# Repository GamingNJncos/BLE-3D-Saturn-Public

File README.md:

# BLE-3D #
Sega Saturn 3D Controller Bluetooth(BLE) Adapter

# **What does it do?** #
- This is an open source and completely solderless adapter for the Sega Saturn 3D Controller that converts it to a Bluetooth(BLE) HID Gamepad. 
- The end result demonstrates a battery powered and solderless adapter that allows you to use one of the best controllers ever made to date across numerous consoles

### Highlights ###
- **Zero modifications to the factory controller** are neccesary to build, test, or play with this adapter.
- Both Analog, and Digital mode (switch on controller) are fully supported
- Want to revert back to OE? Simply plug the OE cable back in. 
- Latency testing pin on-pcb offers consistent and reproducible testing across code changes and development

### Lowlights ###
- This isn't a "retail ready product", it's a proof of concept
- No case for this has been published yet (bare pcb)
- Power circuit has a couple issues. More details in Caveats section

# **Compatibility** #
 This is an area I'm extremely proud of as of writing the BLE3D is known to work with: 
  - Windows, Linux, and Steamdeck
  - ALL supported [Blueretro](https://github.com/darthcloud/BlueRetro) consoles 
  - That means the 3D is now available on (in no particular order)
        - NeoGeo, Supergun, JAMMA
	- Atari 2600/7800, Master System
	- NES, PCE / TG16, Mega Drive / Genesis, SNES
	- CD-i, 3DO, Jaguar, Saturn, PSX, PC-FX, 
	- JVS (Arcade), Virtual Boy, N64, Dreamcast, PS2, GameCube & Wii
	- I'm sure I'm missing a handful
 
  - Note: the analog pad/triggers support are per console, there is no 'digital emulation' on the analog stick.

# **Background** #
For years I've dreamed of a wireless Sega Saturn 3d Pad, just like the patents intended.

- [US Patent Number US 7488,254 B2](https://patentimages.storage.googleapis.com/a2/97/47/e77a8c63165461/US7488254.pdf)
- [US Patent Number Des. 409, 149](https://patentimages.storage.googleapis.com/3d/96/ad/edd675699738cf/USD409149.pdf)
- [European Patent Number EP 1 332 778 B1](https://patentimages.storage.googleapis.com/ed/ba/17/c22422d5d3cc47/EP1332778B1.pdf)

Fast forward many years, I stumbled across some work [Hexfreq](https://twitter.com/hexfreq) was doing with arduino and asked if I could take a look at the code. The rest is history.
From there [Humble Bazooka](https://twitter.com/humblebazooka) and I have spent countless hours to make sure this was a reality. I'd be remissed to leave out [darthcloud](https://twitter.com/darthcloud64) has also been an immense help along the way.

# **PCBs** #
- There are 2 publicly available DIY pcb's for "dev kits". 
- There are various issues or design misses with both pcbs
- They aren't intended for retail use, but you can build one yourself **today**.
- Beveling the controller facing pins is advised 

## **LightWing** ##
 - This is a 'new' revision of the BLE-Saturn-3D that focuses on core functionality. This was optimized as the low cost option for home builders. At current, this is the advised version to use until development can progress farther on the extra features of the HeavyWing 
- PCB: https://oshpark.com/shared_projects/7RqwDWJT 
<BR>  <BR>

## **HeavyWing** ##
- The original PCB. Take the above patents put them in a blender. It adds LCD Support, Motion Controls & Rumble. You can use the LightWing code (better performance) on a Heavywing PCB but will need to change some pin mappings.
- PCB: https://oshpark.com/shared_projects/ki7HbZV4
<BR>  <BR><BR> 

# **BOM** #
## LightWing ###
 - 1x [LightWing PCB](https://oshpark.com/shared_projects/7RqwDWJT)
 - 1x [Adafruit Feather Huzzah32](https://www.adafruit.com/product/3405)
 - 1x Battery
<BR><BR> 
	
## HeavyWing ##
 - 1x [HeavyWing PCB](https://oshpark.com/shared_projects/ki7HbZV4)
 - 1x [Adafruit Feather Huzzah32](https://www.adafruit.com/product/3405) 
 - 1x [HiLetgo GY-521 AKA MPU-6050 Tilt Sensor](http://hiletgo.com/ProductDetail/2157948.html)*  (optional - while it does "work" the kalman filter needs some rework. Must support 3.3v, some are 5v only) 
- 1x OLED 128X64 SSD1306 (optional)
- 1x 3.3v Rumble Motor* (optional - this circuit is not populated on the PCB currently)
- 1x Battery
<BR><BR> 

# **Assembly** #
- Assembly is straightforward, it's just a PCB sandwhich and some solder
- Orientation might be counter intuitive

 ### **LightWing - Assembly** ###
- When you build this lay Segata Face-Down, then set the Feather through the holes with the ESP, USB, and Battery plug facing you
- This provies some additional space for the battery directly under the PCB which would closet match the original patent docs visually
<BR>  <BR>

 ### **LightWing - Installation** ###
- Sega Logo and Button Face top
- Segata faces triggers or back of controller
<BR>   <BR>  <BR>

  ### **HeavyWing - Assembly** ###
   - *Pictures to be uploaded soon*
  
<BR><BR>  
# **Before you compile the code** #
- [PlatformIO installed in VScode](https://docs.platformio.org/en/stable/tutorials/espressif32/arduino_debugging_unit_testing.html), the [platformio.ini](https://github.com/GamingNJncos/BLE-3D-Saturn-Public/blob/main/platformio.ini), and the main.cpp for the Lightwing or the Heavywing
- This has not been tested with Arduino IDE extensively but should compile fine however extremely slow
- If you are mixing and matching LightWing code with the HeavyWing PCB, make sure you change the pinmapping. 
- This is well documented in the code if you jump to "Pinmappings for your PCB version"

## Powering the Device ##
This is direct from the [Adafruit Documentation](https://learn.adafruit.com/adafruit-huzzah32-esp32-feather/power-management)
- There's two ways to power a Feather:
- **You can connect with a USB cable** (just plug into the jack) and the Feather will regulate the 5V USB down to 3.3V.
-  **You can also connect a 4.2/3.7V Lithium Polymer** (LiPo/LiPoly) or Lithium Ion (LiIon) battery to the JST jack. This will let the Feather run on a rechargeable battery.
-  **When the USB power is powered, it will automatically switch over to USB for power**, as well as start charging the battery (if attached). 
- **This happens 'hot-swap' style** so you can always keep the LiPoly connected as a 'backup' power that will only get used when USB power is lost.

<BR><BR> 
# **Caveats and Gotchas** #
 ## A Note on the Huzzah32 revisions ##
  - Check your WROOM version before flashing!
  - There is a NEW revision of the huzzah32 shipping with the Wroom-32-**E** that will have some problems initially when plugged into the controller
  - This is a result of changes to pin IO12 between the D and E modules (and a bootstrap pin) 
  - PCB's were made based on result on the Wroom-32-**D** module and have no issues "out of the box"
  
  - On Wroom-E when the pcb is plugged into the controller at boot similar to boot:0x33 (SPI_FAST_FLASH_BOOT) **invalid header: 0xffffffff**
  - You can burn an efuse to work around this with the espefuse tool. Note this is irreversible, if you are uncomfortable with this try to find another vendor with the 32D in stock   - How to burn the efuse: `espefuse.py --port [com port] --baud 115200 set_flash_voltage 3.3V` confirm the fuse status with `espefuse -p [com port] --baud 115200 summary`. At the bottom it will say **Flash voltage (VDD_SDIO) set to 3.3V by efuse.**
- At the bottom it will say **Flash voltage (VDD_SDIO) set to 3.3V by efuse.**

 ## Battery Warning ##
  - It is *extremely* important that you check the polarity on your battery jack is oriented correctly. There is 0 polarity protection. The charging circuit WILL fry if you plug it in and it's backwards.

 ## Powering Down ##
  - Due to the design of the adafruit feather (esp32) there is no formal power switch. 
  - You must either solder a physical switch on to the battery, **or** unplug it. This is not always easy with the JST connector used so be careful.
 
  ## Charging ##
   - Another unfortunate aspect of the power circuit design on the feather is that the device must be powered on to charge. 
   - There is no "charging mode" so anytime the controller needs to charge it will be broadcasting. 
   - Deep sleep is the best solution for this long term but there are reassons it's not included just yet.

  ## Missing Trigger ##
   - In windows if you go to look at the button inputs in joy.cpl the right trigger is not displayed.  
   - The trigger is there, but you have to use another pad tester to "see it".
  - The picture below *is the expected behavior* and appears to be a problem with joy.cpl in particular.
	<BR> <BR> <BR>

## Various Demos and feature teasers ##
- [Taking Nights for a spin over Bluetooth](https://twitter.com/GamingNJncos/status/1537364206881755136)
- [LCD and customizable Boot Logo](https://twitter.com/GamingNJncos/status/1532819934551724033)
- [Pad Test Demo in X-Men COTA](https://twitter.com/GamingNJncos/status/1537362477817765889)
- [Steamdek Test](https://twitter.com/GamingNJncos/status/1540845741710745602)
- [Early External Unit Testing](https://twitter.com/GamingNJncos/status/1404144038693986307)

## Latency Testing ##
- A significant amount of consideration went into making it easy to test code changes and the impact on latency
- The Lightwing PCB has a dedicated solder pad for consistent testing methodology and code incorporates easy to toggle enable/disable for the pin
- Documentation on the process is available [here](https://github.com/GamingNJncos/BLE-3D-Saturn-Public/tree/main/BlueRetro_Latency_Testing)

## **Note on the Boot Logos (Supported on HeavyWing PCB)** ##
This is documented in the code however if you want to convert images [this tool](https://lcd-image-converter.riuson.com/en/about/) is really useful  
<BR>  <BR>

## Whats with the Names? ##
- Feather add-ons or expansions (hat equivalent for raspberry pi) are called "Wings". 
- Combine that with some Sega nerd-lore and you the [Heavy Wing](https://panzerdragoon.fandom.com/wiki/Heavy_Wing) and [Light Wing](https://panzerdragoon.fandom.com/wiki/Light_Wing)

<BR><BR>

# **Strange notes and pedantic details** #
 ## Protocol Details and Resources ##
 - [A great overview across numerous sega consoles](https://hackaday.io/project/170365-blueretro/log/180790-evolution-of-segas-io-interface-from-sg-1000-to-saturn) by [darthcloud](https://twitter.com/darthcloud64)
 - [Additional protocol details for the Saturn](http://forums.modretro.com/index.php?threads/saturn-controller-protocol-mk80116-mk80100.11328/)

 ## Saturn 3D supported Game list, patent details, and more ##
https://segaretro.org/3D_Control_Pad
 
 ## Polling Oddity or Opportunity? ## 
The [Saturn only polls the 3D protocol at 16ms intervals](https://nfggames.com/forum2/index.php?topic=5055.0) (screen blank). There is however some suggestion in the below post that the Action Replay (this is firmware version specific) can attempt polling faster.  It's worth taking a look at as it may be possible to force games into a faster mode with patching.

Qoute:
"For whatever reason, it's only polling the controller for 14.25ms, with around 310us pauses in between, so it's polling much quicker, but the real issue is after this 14.25ms is up, it then drives the SEL line Hi and goes about it's business for ~2.5ms after that, then back to polling."

## Other demos and informational links ##
- [A DIY internal BlueRetro receiver for Saturn](https://twitter.com/nosIndulgences/status/1573719805496299520)
- [Hexfreq showing off a completely differnt bluetooth saturn solution](https://twitter.com/hexfreq/status/1468282054978818062)

## **Libraries in use** ##
- [ESP32-BLE-Gamepad](https://github.com/lemmingDev/ESP32-BLE-Gamepad)
 - This is subject to change long term as new and improved libraries emerge to support BLE HID gamepads

- [NimBLE-Arduino](https://github.com/h2zero/NimBLE-Arduino)

## **Details on the Feather** ##
- If you want to remix the PCB's or understand more about the feather itself check out the following
- [Feather Pinouts and hardware overview](https://learn.adafruit.com/adafruit-huzzah32-esp32-feather/pinouts)

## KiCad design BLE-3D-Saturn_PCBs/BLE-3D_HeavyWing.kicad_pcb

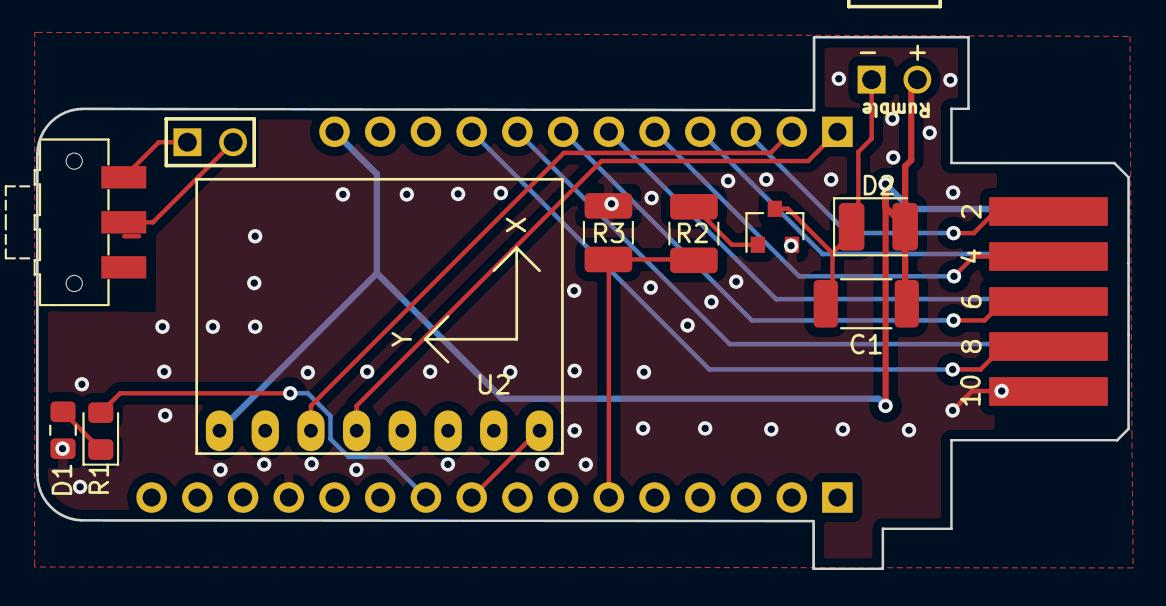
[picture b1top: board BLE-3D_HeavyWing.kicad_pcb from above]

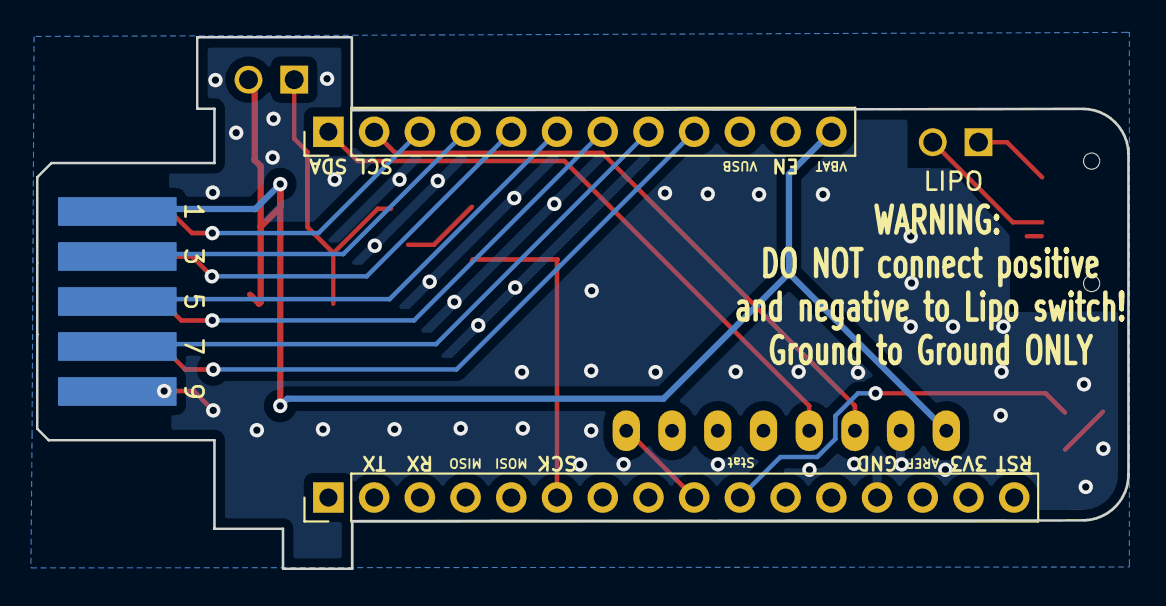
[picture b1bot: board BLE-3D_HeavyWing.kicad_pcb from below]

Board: 2 copper layers, 60.6 x 29.5 mm, 14 parts (3 on the bottom side), 18 nets.

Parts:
-  +: HEADER-FEMALE-2POS-TH-1x02-JST-PH; HEADER1x2HF
C1: C_Small; C_2010_5025Metric
D1: LED_Small; R_0805_2012Metric_Pad1.15x1.40mm_HandSolder
D2: DIODE; D_1210_3225Metric_Pad1.42x2.65mm_HandSolder
J1: feather long; PinHeader_1x16_P2.54mm_Vertical
J2: feather short; PinHeader_1x12_P2.54mm_Vertical
LIPO: HEADER1X2; HEADER1x2V
Q1: 2N7002; SOT-23
R1: R_Small; LED_0805_2012Metric_Pad1.15x1.40mm_HandSolder
R2, R3: R_Small; R_1210_3225Metric_Pad1.42x2.65mm_HandSolder
SW1: Power; SW_SPDT_CK-JS102011SAQN
U1: Saturn_3D_Pinout; Saturn_Controller_Pinout_2
U2: GY-521

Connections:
BAT_GND: LIPO.1, LIPO.2, SW1.1, SW1.2
BatLED: J1.10, R1.2
D0: J2.4, U1.3
D1: J2.3, U1.2
D2: J2.9, U1.8
D3: J2.8, U1.7
GND: D1.1, J1.13, Q1.2, R3.1, U1.9, U1.10, U2.2
INT: J1.9, U2.8
unnamed: - +.1, C1.2, D2.1, Q1.3
unnamed: D1.2, R1.1
unnamed: Q1.1, R2.2
SCL: J2.2, U2.3
SDA: J2.1, U2.4
TH: J2.5, U1.4
TL: J2.7, U1.6
TR: J2.6, U1.5
VBAT: - +.2, C1.1, D2.2, J2.12, U1.1, U2.1
VibeOut: J1.6, R2.1, R3.2

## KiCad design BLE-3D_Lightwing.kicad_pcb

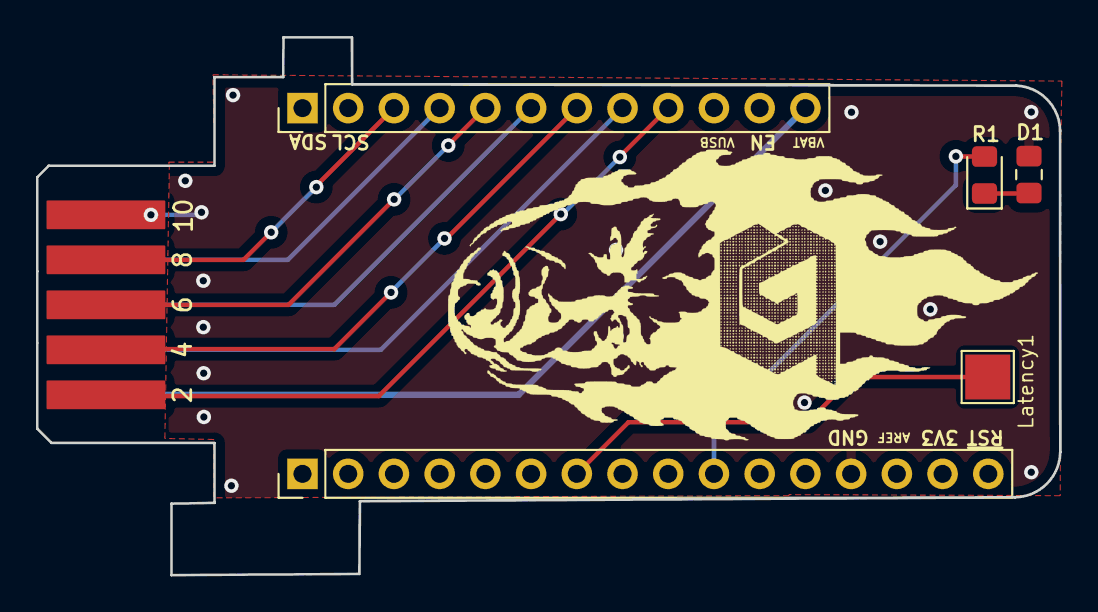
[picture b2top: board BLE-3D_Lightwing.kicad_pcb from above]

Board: 2 copper layers, 56.8 x 29.9 mm, 6 parts (1 on the bottom side), 12 nets.

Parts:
D1: LED_Small; R_0805_2012Metric_Pad1.15x1.40mm_HandSolder
J1: feather long; PinHeader_1x16_P2.54mm_Vertical
J2: feather short; PinHeader_1x12_P2.54mm_Vertical
Latency1: Latency; TestPoint_Pad_2.5x2.5mm
R1: R_Small; LED_0805_2012Metric_Pad1.15x1.40mm_HandSolder
U1: Saturn_3D_Pinout; Saturn_Controller_Pinout_2

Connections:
BatLED: J1.10, R1.2
D0: J2.8, U1.3
D1: J2.9, U1.2
D2: J2.3, U1.8
D3: J2.4, U1.7
GND: D1.1, J1.13, U1.9, U1.10
Latency: J1.7, Latency1.1
unnamed: D1.2, R1.1
TH: J2.7, U1.4
TL: J2.5, U1.6
TR: J2.6, U1.5
VBAT: J2.12, U1.1

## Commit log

2022-11-01 Initial code release
    Come checkout my bugs
2022-11-02 Add kicad PCB exports for direct Download
2022-11-02 Add PCBs
2022-11-02 How to test latency with Blueretro
2022-11-08 Update and rename Notes.txt to How_To_Latency_Test
2022-11-08 Readme.md
    rename
2022-11-08 Rename How_To_Latency_Test to Readme.md
2022-11-08 Rename Readme.md to README.md
2022-11-08 Update README.md
    Updated Latency Test info - Still under construction
2023-05-17 Add Lightwing fork
2023-05-18 Create main.cpp
    High Performance Firmware
2023-05-19 Migrate old main.cpp to dedicated folder
2023-05-19 Delete ESP-32_PlatformIO_code directory
    rm
2023-06-11 Update README.md
    Wroom-32-E Notes and Power
